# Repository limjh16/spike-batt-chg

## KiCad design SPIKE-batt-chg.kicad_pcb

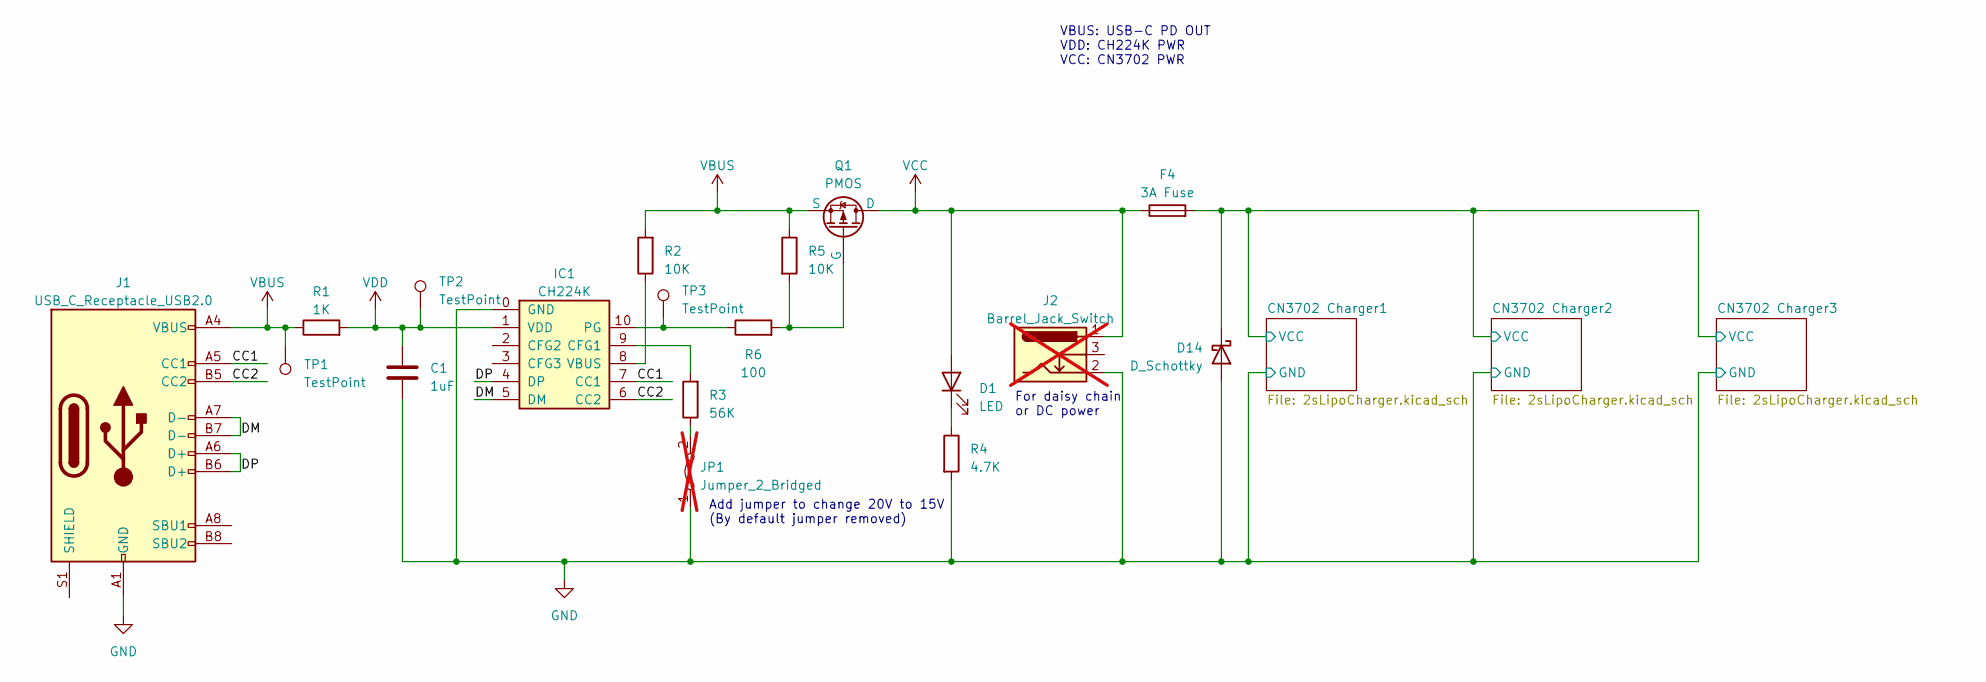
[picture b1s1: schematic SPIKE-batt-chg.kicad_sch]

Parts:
C1: 1uF; C_0603_1608Metric
D1: LED; LED_0603_1608Metric; Part XL-1606UGC; JLCPCB Part # C965863
D14: D_Schottky; D_SMA; Part SS54; JLCPCB Part # C22452
F4: 3A Fuse; Fuse_0603_1608Metric; Part F0603FA3000V032T; JLCPCB Part # C96544
IC1: CH224K; ESSOP-10_3.9x4.9mm_P1.00mm_EP2.3x3.2mm_ThermalVias
J1: USB_C_Receptacle_USB2.0; USB_C_Receptacle_XKB_U262-16XN-4BVC11; Part TYPE-C 16PIN 2MD(073); JLCPCB Part # C2765186
J2: Barrel_Jack_Switch; BarrelJack_Lock; not fitted
JP1: Jumper_2_Bridged; TestPoint_2Pads_Pitch2.54mm_Drill0.8mm; not fitted
Q1: PMOS; SOT-23; Part AO3401A; JLCPCB Part # C15127
R1: 1K; R_0603_1608Metric
R2, R5: 10K; R_0603_1608Metric
R3: 56K; R_0603_1608Metric
R4: 4.7K; R_0603_1608Metric
R6: 100; R_0603_1608Metric
TP1, TP2, TP3: TestPoint; TestPoint_Pad_D1.0mm

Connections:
/CC1: IC1.7 (CC1), J1.A5 (CC1)
/CC2: IC1.6 (CC2), J1.B5 (CC2)
/CN3702 Charger1/VCC: D14.1 (K), F4.2; also elsewhere on the board
/DM: IC1.5 (DM), J1.A7 (D-), J1.B7 (D-)
/DP: IC1.4 (DP), J1.A6 (D+), J1.B6 (D+)
GND: C1.2, D14.2 (A), IC1.0 (GND), J1.A1 (GND), J1.A12 (GND), J1.B1 (GND), J1.B12 (GND), J2.2, JP1.1 (A), R4.2; also elsewhere on the board
unnamed: D1.1 (K), R4.1
unnamed: IC1.9 (CFG1), R3.2
unnamed: IC1.10 (PG), R6.1, TP3.1
unnamed: IC1.8 (VBUS), R2.1
unnamed: JP1.2 (B), R3.1
unnamed: Q1.2 (G), R5.2, R6.2
VBUS: J1.A4 (VBUS), J1.A9 (VBUS), J1.B4 (VBUS), J1.B9 (VBUS), Q1.3 (S), R1.1, R2.2, R5.1, TP1.1
VCC: D1.2 (A), F4.1, J2.1, Q1.1 (D)
VDD: C1.1, IC1.1 (VDD), R1.2, TP2.1

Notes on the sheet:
VBUS: USB-C PD OUT VDD: CH224K PWR VCC: CN3702 PWR
For daisy chain or DC power
Add jumper to change 20V to 15V (By default jumper removed)

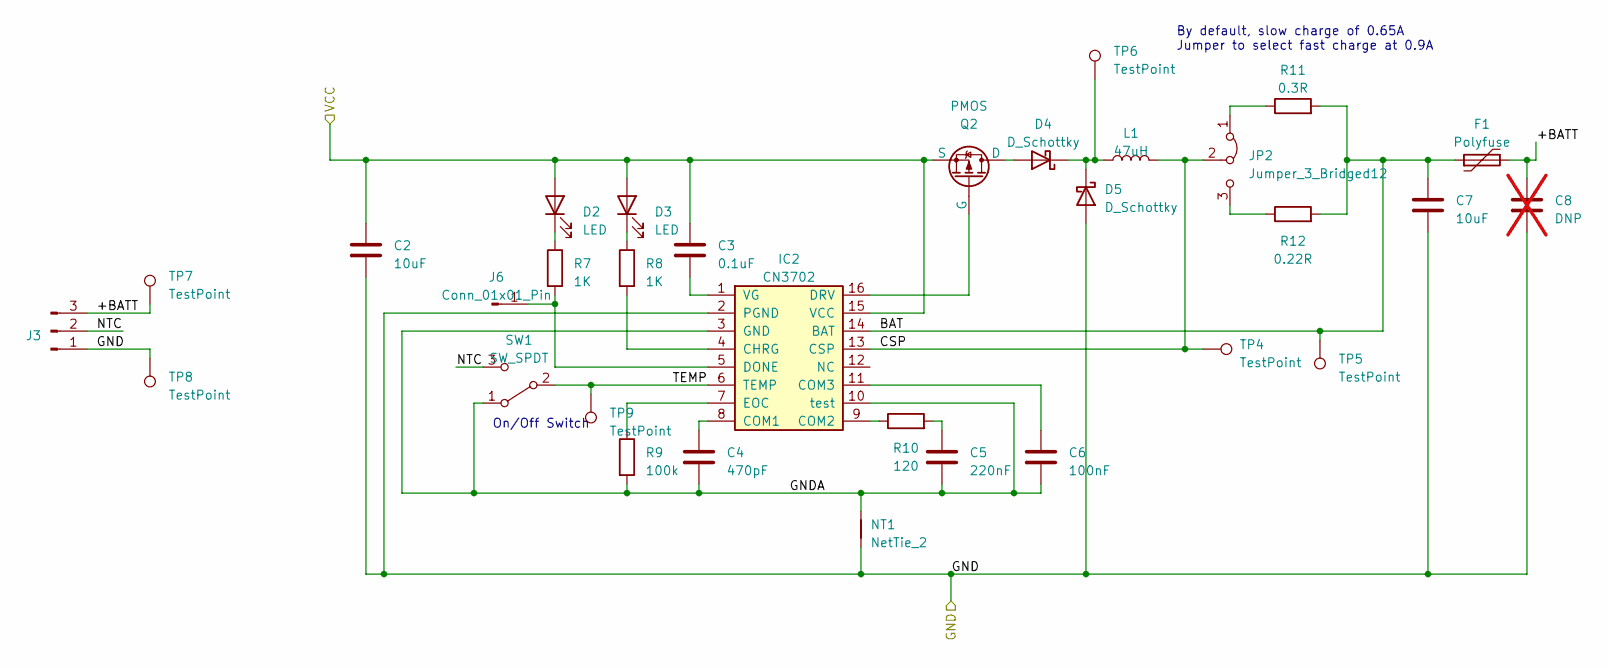
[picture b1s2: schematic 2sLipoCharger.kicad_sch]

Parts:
C2, C7: 10uF; C_0603_1608Metric
C3: 0.1uF; C_0603_1608Metric
C4: 470pF; C_0603_1608Metric
C5: 220nF; C_0603_1608Metric
C6: 100nF; C_0603_1608Metric
C8: DNP; C_0603_1608Metric; not fitted
D2: LED; LED_0603_1608Metric; Part XL-1606UGC; JLCPCB Part # C965863
D3: LED; LED_0603_1608Metric; Part XL-1606SURC; JLCPCB Part # C965860
D4, D5: D_Schottky; D_SOD-123; Part B5819W SL; JLCPCB Part # C8598
F1: Polyfuse; R_1812_4532Metric; Part MF-MSMF110/16-2; JLCPCB Part # C210834
IC2: CN3702; TSSOP-16_4.4x5mm_P0.65mm
J3: Conn_01x03_Pin; BladeConn_1x03_P2.00mm_Lock
J6: Conn_01x01_Pin; PinHeader_1x01_P2.54mm_Vertical
JP2: Jumper_3_Bridged12; 1X03_LOCK
L1: 47uH; L_Sunlord_SWPA6045S; Part YNR6045-470M; JLCPCB Part # C497841
NT1: NetTie_2; NetTie-2_SMD_Pad0.5mm
Q2: PMOS; SOT-23; Part AO3401A; JLCPCB Part # C15127
R7, R8: 1K; R_0603_1608Metric
R9: 100k; R_0603_1608Metric; JLCPCB Part # C25803
R10: 120; R_0603_1608Metric
R11: 0.3R; R_0603_1608Metric; Part FRL0603JR300TS; JLCPCB Part # C2934256
R12: 0.22R; R_0603_1608Metric; Part FRL0603FR220TS; JLCPCB Part # C3013347
SW1: SW_SPDT; SW_SPDT_PCM12; Part MSK12C02-HB; JLCPCB Part # C431541
TP4, TP5, TP6, TP7, TP8, TP9: TestPoint; TestPoint_Pad_D1.0mm

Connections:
/CN3702 Charger1/+BATT: C8.1, F1.2, J3.3, TP7.1
/CN3702 Charger1/BAT: C7.1, F1.1, IC2.14 (BAT), R11.2, R12.2, TP5.1
/CN3702 Charger1/CSP: IC2.13 (CSP), JP2.2 (C), L1.2, TP4.1
/CN3702 Charger1/GNDA: C4.2, C5.2, C6.2, IC2.3 (GND), IC2.10 (test), NT1.2, R9.2, SW1.1 (A)
/CN3702 Charger1/NTC: J3.2, SW1.3 (C)
/CN3702 Charger1/TEMP: IC2.6 (TEMP), SW1.2 (B), TP9.1
/CN3702 Charger1/VCC: C2.1, C3.1, D2.2 (A), D3.2 (A), IC2.15 (VCC), Q2.3 (S); also elsewhere on the board
GND: C2.2, C7.2, C8.2, D5.2 (A), IC2.2 (PGND), J3.1, NT1.1, TP8.1; also elsewhere on the board
unnamed: C5.1, R10.2
unnamed: D2.1 (K), R7.1
unnamed: D3.1 (K), R8.1
unnamed: D4.2 (A), Q2.1 (D)
unnamed: D4.1 (K), D5.1 (K), L1.1, TP6.1
unnamed: IC2.4 (CHRG), R8.2
unnamed: C4.1, IC2.8 (COM1)
unnamed: IC2.9 (COM2), R10.1
unnamed: C6.1, IC2.11 (COM3)
unnamed: IC2.5 (DONE), J6.1, R7.2
unnamed: IC2.16 (DRV), Q2.2 (G)
unnamed: IC2.7 (EOC), R9.1
unnamed: C3.2, IC2.1 (VG)
unnamed: JP2.1 (A), R11.1
unnamed: JP2.3 (B), R12.1

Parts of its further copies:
C9, C14, C16, C21: 10uF; C_0603_1608Metric
C10, C17: 0.1uF; C_0603_1608Metric
C11, C18: 470pF; C_0603_1608Metric
C12, C19: 220nF; C_0603_1608Metric
C13, C20: 100nF; C_0603_1608Metric
C15, C22: DNP; C_0603_1608Metric; not fitted
D6, D10: LED; LED_0603_1608Metric; Part XL-1606UGC; JLCPCB Part # C965863
D7, D11: LED; LED_0603_1608Metric; Part XL-1606SURC; JLCPCB Part # C965860
D8, D9, D12, D13: D_Schottky; D_SOD-123; Part B5819W SL; JLCPCB Part # C8598
F2, F3: Polyfuse; R_1812_4532Metric; Part MF-MSMF110/16-2; JLCPCB Part # C210834
IC3, IC4: CN3702; TSSOP-16_4.4x5mm_P0.65mm
J4, J5: Conn_01x03_Pin; BladeConn_1x03_P2.00mm_Lock
J7, J8: Conn_01x01_Pin; PinHeader_1x01_P2.54mm_Vertical
JP3, JP4: Jumper_3_Bridged12; 1X03_LOCK
L2, L3: 47uH; L_Sunlord_SWPA6045S; Part YNR6045-470M; JLCPCB Part # C497841
NT2, NT3: NetTie_2; NetTie-2_SMD_Pad0.5mm
Q3, Q4: PMOS; SOT-23; Part AO3401A; JLCPCB Part # C15127
R13, R14, R19, R20: 1K; R_0603_1608Metric
R15, R21: 100k; R_0603_1608Metric; JLCPCB Part # C25803
R16, R22: 120; R_0603_1608Metric
R17, R23: 0.3R; R_0603_1608Metric; Part FRL0603JR300TS; JLCPCB Part # C2934256
R18, R24: 0.22R; R_0603_1608Metric; Part FRL0603FR220TS; JLCPCB Part # C3013347
SW2, SW3: SW_SPDT; SW_SPDT_PCM12; Part MSK12C02-HB; JLCPCB Part # C431541
TP10, TP11, TP12, TP13, TP14, TP15, TP16, TP17, TP18, TP19, TP20, TP21: TestPoint; TestPoint_Pad_D1.0mm

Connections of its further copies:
/CN3702 Charger1/VCC: C9.1, C10.1, C16.1, C17.1, D6.2 (A), D7.2 (A), D10.2 (A), D11.2 (A), IC3.15 (VCC), IC4.15 (VCC), Q3.3 (S), Q4.3 (S); also elsewhere on the board
/CN3702 Charger2/+BATT: C15.1, F2.2, J4.3, TP10.1
/CN3702 Charger2/BAT: C14.1, F2.1, IC3.14 (BAT), R17.2, R18.2, TP15.1
/CN3702 Charger2/CSP: IC3.13 (CSP), JP3.2 (C), L2.2, TP14.1
/CN3702 Charger2/GNDA: C11.2, C12.2, C13.2, IC3.3 (GND), IC3.10 (test), NT2.2, R15.2, SW2.1 (A)
/CN3702 Charger2/NTC: J4.2, SW2.3 (C)
/CN3702 Charger2/TEMP: IC3.6 (TEMP), SW2.2 (B), TP12.1
/CN3702 Charger3/+BATT: C22.1, F3.2, J5.3, TP16.1
/CN3702 Charger3/BAT: C21.1, F3.1, IC4.14 (BAT), R23.2, R24.2, TP21.1
/CN3702 Charger3/CSP: IC4.13 (CSP), JP4.2 (C), L3.2, TP20.1
/CN3702 Charger3/GNDA: C18.2, C19.2, C20.2, IC4.3 (GND), IC4.10 (test), NT3.2, R21.2, SW3.1 (A)
/CN3702 Charger3/NTC: J5.2, SW3.3 (C)
/CN3702 Charger3/TEMP: IC4.6 (TEMP), SW3.2 (B), TP18.1
GND: C9.2, C14.2, C15.2, C16.2, C21.2, C22.2, D9.2 (A), D13.2 (A), IC3.2 (PGND), IC4.2 (PGND), J4.1, J5.1, NT2.1, NT3.1, TP11.1, TP17.1; also elsewhere on the board
unnamed: C12.1, R16.2
unnamed: C19.1, R22.2
unnamed: D6.1 (K), R13.1
unnamed: D7.1 (K), R14.1
unnamed: D8.2 (A), Q3.1 (D)
unnamed: D8.1 (K), D9.1 (K), L2.1, TP13.1
unnamed: D10.1 (K), R19.1
unnamed: D11.1 (K), R20.1
unnamed: D12.2 (A), Q4.1 (D)
unnamed: D12.1 (K), D13.1 (K), L3.1, TP19.1
unnamed: IC3.4 (CHRG), R14.2
unnamed: C11.1, IC3.8 (COM1)
unnamed: IC3.9 (COM2), R16.1
unnamed: C13.1, IC3.11 (COM3)
unnamed: IC3.5 (DONE), J7.1, R13.2
unnamed: IC3.16 (DRV), Q3.2 (G)
unnamed: IC3.7 (EOC), R15.1
unnamed: C10.2, IC3.1 (VG)
unnamed: IC4.4 (CHRG), R20.2
unnamed: C18.1, IC4.8 (COM1)
unnamed: IC4.9 (COM2), R22.1
unnamed: C20.1, IC4.11 (COM3)
unnamed: IC4.5 (DONE), J8.1, R19.2
unnamed: IC4.16 (DRV), Q4.2 (G)
unnamed: IC4.7 (EOC), R21.1
unnamed: C17.2, IC4.1 (VG)
unnamed: JP3.1 (A), R17.1
unnamed: JP3.3 (B), R18.1
unnamed: JP4.1 (A), R23.1
unnamed: JP4.3 (B), R24.1

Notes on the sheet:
By default, slow charge of 0.65A Jumper to select fast charge at 0.9A
On/Off Switch

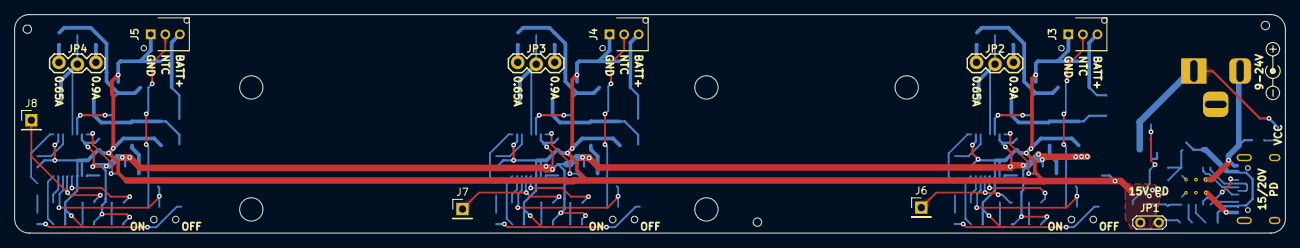
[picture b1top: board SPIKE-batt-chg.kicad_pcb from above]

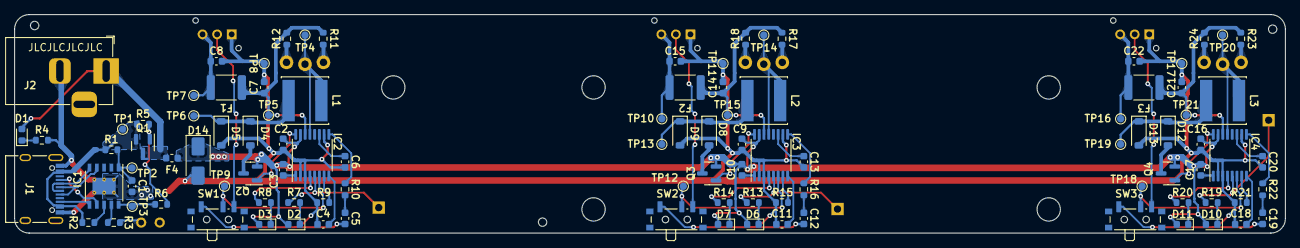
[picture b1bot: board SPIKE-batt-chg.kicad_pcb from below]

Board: 2 copper layers, 174.5 x 30.0 mm, 114 parts (104 on the bottom side), 78 nets.

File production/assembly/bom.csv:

Designator,Footprint,Quantity,Value,LCSC Part #
C1,0603,1,1uF,
"C10, C17, C3",0603,3,0.1uF,
"C11, C18, C4",0603,3,470pF,
"C12, C19, C5",0603,3,220nF,
"C13, C20, C6",0603,3,100nF,
"C14, C16, C2, C21, C7, C9",0603,6,10uF,
"D1, D10, D2, D6",0603,4,LED,C965863
"D11, D3, D7",0603,3,LED,C965860
"D12, D13, D4, D5, D8, D9",D_SOD-123,6,D_Schottky,C8598
D14,D_SMA,1,D_Schottky,C22452
"F1, F2, F3",1812,3,Polyfuse,C210834
F4,0603,1,3A Fuse,C96544
IC1,ESSOP-10_3.9x4.9mm_P1.00mm_EP2.3x3.2mm_ThermalVias,1,CH224K,
"IC2, IC3, IC4",TSSOP-16_4.4x5mm_P0.65mm,3,CN3702,
J1,USB_C_Receptacle_XKB_U262-16XN-4BVC11,1,USB_C_Receptacle_USB2.0,C2765186
"L1, L2, L3",L_Sunlord_SWPA6045S,3,47uH,C497841
"Q1, Q2, Q3, Q4",SOT-23,4,PMOS,C15127
"R1, R13, R14, R19, R20, R7, R8",0603,7,1K,
"R10, R16, R22",0603,3,120,
"R11, R17, R23",0603,3,0.3R,C2934256
"R12, R18, R24",0603,3,0.22R,C3013347
"R15, R21, R9",0603,3,100k,C25803
"R2, R5",0603,2,10K,
R3,0603,1,56K,
R4,0603,1,4.7K,
R6,0603,1,100,
"SW1, SW2, SW3",SW_SPDT_PCM12,3,SW_SPDT,C431541

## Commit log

2023-05-20 Initial Commit: USB-C PD done
2023-05-22 Finished CN3702 battery charging IC schematic
    Added PG switch for CN3702, since the UVLO(min) is 4.6V
    Yet to do: selection of schottky diode and power PMOS
2023-05-22 Split charger into hierarchical sheets 4 charging circuits will be on the board Added jumper for PD voltage selection (9V or 20V) Added SPDT switch to TEMP pin to turn on/off charger
2023-05-23 Finished Schematic
    - Cleaned up page 1
    - Only 3 chargers / board now
    - LED no longer activated by PG, connected to VCC after the P-MOSFET instead
    - Added DC barrel jack for daisy chaining (using M-M 30cm cable)
    - Added jumper to enable fast charge
    - Selected inductor, diode, P-MOSFET, current sense resistor
2023-05-25 Footprint assignment partially done
    - incomplete: minor edit of footprints, locking pin header footprints
    - changed LEDs to side facing, changed PG LED resistor to 4.7k since
    will be going through 20V
2023-05-26 Finished footprint assignments, added testpoints
    - Added polyfuse
    - Cleaned up schematic (mirrored some components for clarity)
2023-05-26 Edited DRC, started layout
2023-05-28 CH224K Board Layout complete
    - Partial layout of CN3702
    - Fixed the incorrect NetTie on 2sLipoCharger.kicad_sch (More things are supposed to go to AGND)
2023-05-29 Finished charger layout
    - Replace global power symbols in charger schematic with local labels
2023-05-29 Finished layout
    - DRC checked, outline complete
    - Left to do: silkscreen
2023-05-31 Added fuse and shunt diode
    For reverse polarity protection
2023-05-31 Added tooling and mounting holes
    - Added pinout for "done" pin on charger for future use
2023-05-31 Change grid origin, generate production files
2023-05-31 Exclude header pins from BOM
2023-06-18 Fixed problems after PCB fab
    - SOT23 MOSFET footprint does not match part, needs to rotate (rerouting
    not done yet)
    - EOC Resistor set to 100k
2023-06-22 Updated 3D models
2024-05-21 add 3mf file for the 3d printed casing
2024-05-21 Fix the routing for rotated MOSFET
2024-05-24 fixes, drc check
2024-05-24 update JLCPCB part for R9,15,21
2024-05-24 fill zones, generated updated gerber and BOM
